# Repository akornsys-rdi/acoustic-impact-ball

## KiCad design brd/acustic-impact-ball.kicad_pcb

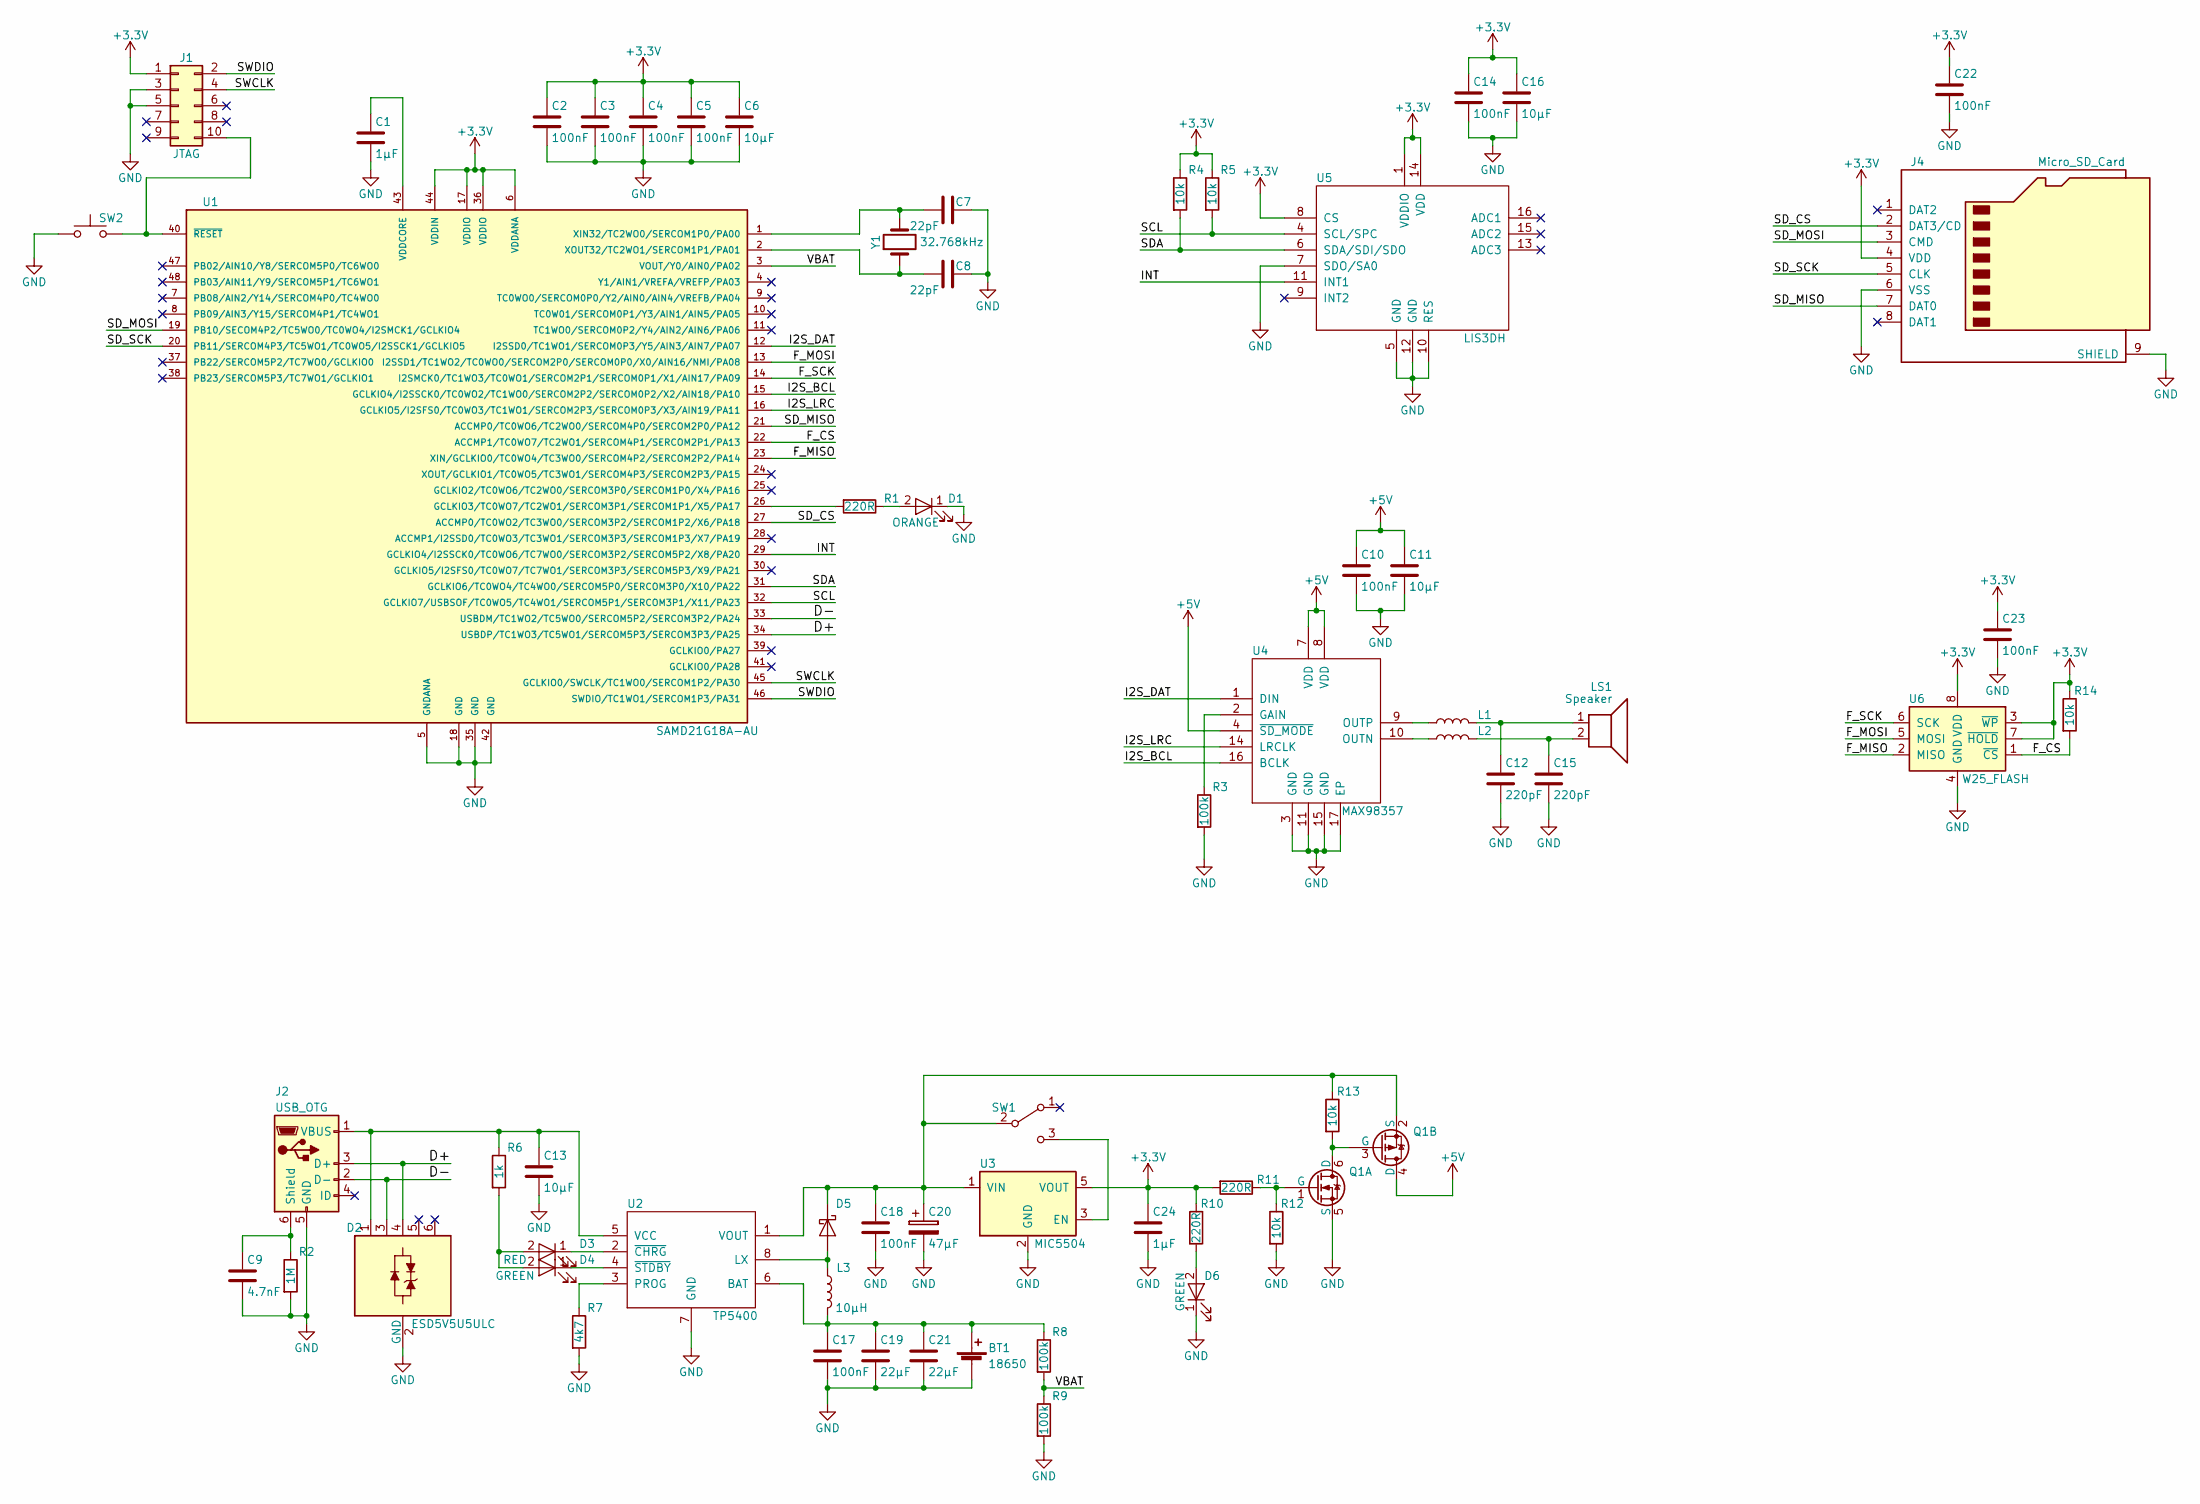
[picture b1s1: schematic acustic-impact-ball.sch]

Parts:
BT1: 18650; 18650-holder
C1, C24: 1µF; C_0805; Manufacturer Part Number C0805C105K8RACTU
C2, C3, C4, C5, C10, C14, C17, C18, C22, C23: 100nF; C_0805; Manufacturer Part Number C0805C104J5RACTU
C6, C11, C13, C16: 10µF; C_0805; Manufacturer Part Number C0805C106K8PACTU
C7, C8: 22pF; C_0805; Manufacturer Part Number C0805C220J5GACTU
C9: 4.7nF; C_0805; Manufacturer Part Number C0805C472K5RACTU
C12, C15: 220pF; C_0805; Manufacturer Part Number C0805C221J5GAC
C19, C21: 22µF; C_0805; Manufacturer Part Number C0805C226M9PACTU
C20: 47µF; CP_Tantalum_Case-B_EIA-3528-21_Reflow; Manufacturer Part Number TAJB476M010TNJ
D1: ORANGE; LED_0805; Manufacturer Part Number LO R976-PS-1
D2: ESD5V5U5ULC; SOT-23-6; Manufacturer Part Number ESD5V5U5ULC E6327
D3: RED; LED_0805; Manufacturer Part Number AP2012SRCPRV
D4, D6: GREEN; LED_0805; Manufacturer Part Number LG R971-KN-1
D5: D_Schottky; D_SOD-123F; Manufacturer Part Number SS34FA
J1: JTAG; Pin_Header_Straight_2x05_Pitch1.27mm_SMD; Manufacturer Part Number 20021121-00010D4LF
J2: USB_OTG; USB_Mini-B; Manufacturer Part Number UJ2-MBH-1-SMT-TR
J4: Micro_SD_Card; 5009010801; Manufacturer Part Number 500901-0801
L1, L2: Ferrite; L_0805_HandSoldering; Manufacturer Part Number BKP2125HS331-T
L3: 10µH; L_Taiyo-Yuden_NR-80xx; Manufacturer Part Number NR8040T100M
LS1: Speaker; Pin_Header_Angled_1x02_Pitch2.54mm; Manufacturer Part Number AS04004PR-R
Q1: DMG6602; SOT-23-6; Manufacturer Part Number DMG6602SVTQ-7
R1, R10, R11: 220R; R_0805_HandSoldering; Manufacturer Part Number CR0805-JW-221ELF
R2: 1M; R_0805_HandSoldering; Manufacturer Part Number CR0805-JW-105ELF
R3: 100k; R_0805_HandSoldering; Manufacturer Part Number CR0805-JW-104ELF
R4, R5, R12, R13, R14: 10k; R_0805_HandSoldering; Manufacturer Part Number CR0805-JW-103ELF
R6: 1k; R_0805_HandSoldering; Manufacturer Part Number CR0805-JW-102ELF
R7: 4k7; R_0805_HandSoldering; Manufacturer Part Number CR0805-JW-472ELF
R8, R9: 100k; R_0805_HandSoldering; Manufacturer Part Number CR0805-FX-1003ELF
SW1: SW_SPDT; SW_SPDT_PCM12; Manufacturer Part Number MSS3-V-T/R
SW2: SW_Push; PTS636_SP50
U1: SAMD21G18A-AU; TQFP-48_7x7mm_Pitch0.5mm; Manufacturer Part Number ATSAMD21G18A-AU
U2: TP5400; SOIC-8-1EP_3.9x4.9mm_Pitch1.27mm
U3: MIC5504; SOT-23-5; Manufacturer Part Number MIC5504-3.3YM5-TR
U4: MAX98357; QFN-16-1EP_3x3mm_Pitch0.5mm; Manufacturer Part Number MAX98357AETE+T
U5: LIS3DH; LGA-16_3x3mm_Pitch0.5mm_Handsoldering; Manufacturer Part Number LIS3DHTR
U6: W25_FLASH; SOIJ-8_5.3x5.3mm_Pitch1.27mm; Manufacturer Part Number W25Q128JVSIQ
Y1: 32.768kHz; Crystal_SMD_3215-2pin_3.2x1.5mm; Manufacturer Part Number FC-135 32.7680KA-A5

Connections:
+3V3: C2.1, C3.1, C4.1, C5.1, C6.1, C14.1, C16.1, C22.1, C23.1, C24.1, J1.1, J4.4 (VDD), R4.1, R5.1, R10.1, R11.2, R14.1, U1.6 (VDDANA), U1.17 (VDDIO), U1.36 (VDDIO), U1.44 (VDDIN), U3.5 (VOUT), U5.1 (VDDIO), U5.8 (CS), U5.14 (VDD), U6.3 (~WP), U6.7 (~HOLD), U6.8 (VDD)
+5V: C10.1, C11.1, Q1.4 (D), U4.4 (~SD_MODE), U4.7 (VDD), U4.8 (VDD)
/D+: D2.4, J2.3 (D+), U1.34 (USBDP/TC1WO3/TC5WO1/SERCOM5P3/SERCOM3P3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)
/D-: D2.3, J2.2 (D-), U1.33 (USBDM/TC1WO2/TC5WO0/SERCOM5P2/SERCOM3P2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)
/F_CS: R14.2, U1.22 (ACCMP1/TC0WO7/TC2WO1/SERCOM4P1/SERCOM2P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), U6.1 (~CS)
/F_MISO: U1.23 (XIN/GCLKIO0/TC0WO4/TC3WO0/SERCOM4P2/SER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), U6.2 (MISO)
/F_MOSI: U1.13 (I2SSD1/TC1WO2/TC0WO0/SERCOM2P0/SERCOM0P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), U6.5 (MOSI)
/F_SCK: U1.14 (I2SMCK0/TC1WO3/TC0WO1/SERCOM2P1/SERCOM0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), U6.6 (SCK)
/I2S_BCL: U1.15 (GCLKIO4/I2SSCK0/TC0WO2/TC1WO0/SERCOM2P2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), U4.16 (BCLK)
/I2S_DAT: U1.12 (I2SSD0/TC1WO1/SERCOM0P3/Y5/AIN3/AIN7/PA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), U4.1 (DIN)
/I2S_LRC: U1.16 (GCLKIO5/I2SFS0/TC0WO3/TC1WO1/SERCOM2P3/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), U4.14 (LRCLK)
/INT: U1.29 (GCLKIO4/I2SSCK0/TC0WO6/TC7WO0/SERCOM3P2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), U5.11 (INT1)
/SCL: R5.2, U1.32 (GCLKIO7/USBSOF/TC0WO5/TC4WO1/SERCOM5P1/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), U5.4 (SCL/SPC)
/SDA: R4.2, U1.31 (GCLKIO6/TC0WO4/TC4WO0/SERCOM5P0/SERCOM3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), U5.6 (SDA/SDI/SDO)
/SD_CS: J4.2 (DAT3/CD), U1.27 (ACCMP0/TC0WO2/TC3WO0/SERCOM3P2/SERCOM1P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)
/SD_MISO: J4.7 (DAT0), U1.21 (ACCMP0/TC0WO6/TC2WO0/SERCOM4P0/SERCOM2P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)
/SD_MOSI: J4.3 (CMD), U1.19 (PB10/SECOM4P2/TC5WO0/TC0WO4/I2SMCK1/GCL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)
/SD_SCK: J4.5 (CLK), U1.20 (PB11/SERCOM4P3/TC5WO1/TC0WO5/I2SSCK1/GC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)
/SWCLK: J1.4, U1.45 (GCLKIO0/SWCLK/TC1WO0/SERCOM1P2/PA30)
/SWDIO: J1.2, U1.46 (SWDIO/TC1WO1/SERCOM1P3/PA31)
/VBAT: R8.2, R9.1, U1.3 (VOUT/Y0/AIN0/PA02)
GND: BT1.2 (-), C1.2, C2.2, C3.2, C4.2, C5.2, C6.2, C7.2, C8.2, C9.2, C10.2, C11.2, C12.2, C13.2, C14.2, C15.2, C16.2, C17.2, C18.2, C19.2, C20.2, C21.2, C22.2, C23.2, C24.2, D1.1 (K), D2.2 (GND), D6.1 (K), J1.3, J1.5, J2.5 (GND), J4.6 (VSS), J4.9 (SHIELD), Q1.5 (S), R2.2, R3.2, R7.2, R9.2, R12.2, SW2.1, U1.5 (GNDANA), U1.18 (GND), U1.35 (GND), U1.42 (GND), U2.7 (GND), U3.2 (GND), U4.3 (GND), U4.11 (GND), U4.15 (GND), U4.17 (EP), U5.5 (GND), U5.7 (SDO/SA0), U5.10 (RES), U5.12 (GND), U6.4 (GND)
unnamed: BT1.1 (+), C17.1, C19.1, C21.1, L3.2, R8.1, U2.6 (BAT)
unnamed: C1.1, U1.43 (VDDCORE)
unnamed: C7.1, U1.1 (XIN32/TC2WO0/SERCOM1P0/PA00), Y1.2
unnamed: C8.1, U1.2 (XOUT32/TC2WO1/SERCOM1P1/PA01), Y1.1
unnamed: C9.1, J2.6 (Shield), R2.1
unnamed: C12.1, L1.2, LS1.1
unnamed: C13.1, D2.1, J2.1 (VBUS), R6.1, U2.5 (VCC)
unnamed: C15.1, L2.2, LS1.2
unnamed: C18.1, C20.1, D5.1 (K), Q1.2 (S), R13.1, SW1.2 (B), U2.1 (VOUT), U3.1 (VIN)
unnamed: D1.2 (A), R1.1
unnamed: D3.1 (K), U2.2 (~CHRG)
unnamed: D3.2 (A), D4.2 (A), R6.2
unnamed: D4.1 (K), U2.4 (~STDBY)
unnamed: D5.2 (A), L3.1, U2.8 (LX)
unnamed: D6.2 (A), R10.2
unnamed: J1.10, SW2.2, U1.40 (~RESET~)
unnamed: L1.1, U4.9 (OUTP)
unnamed: L2.1, U4.10 (OUTN)
unnamed: Q1.1 (G), R11.1, R12.1
unnamed: Q1.3 (G), Q1.6 (D), R13.2
unnamed: R1.2, U1.26 (GCLKIO3/TC0WO7/TC2WO1/SERCOM3P1/SERCOM1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)
unnamed: R3.1, U4.2 (GAIN)
unnamed: R7.1, U2.3 (PROG)
unnamed: SW1.3 (C), U3.3 (EN)

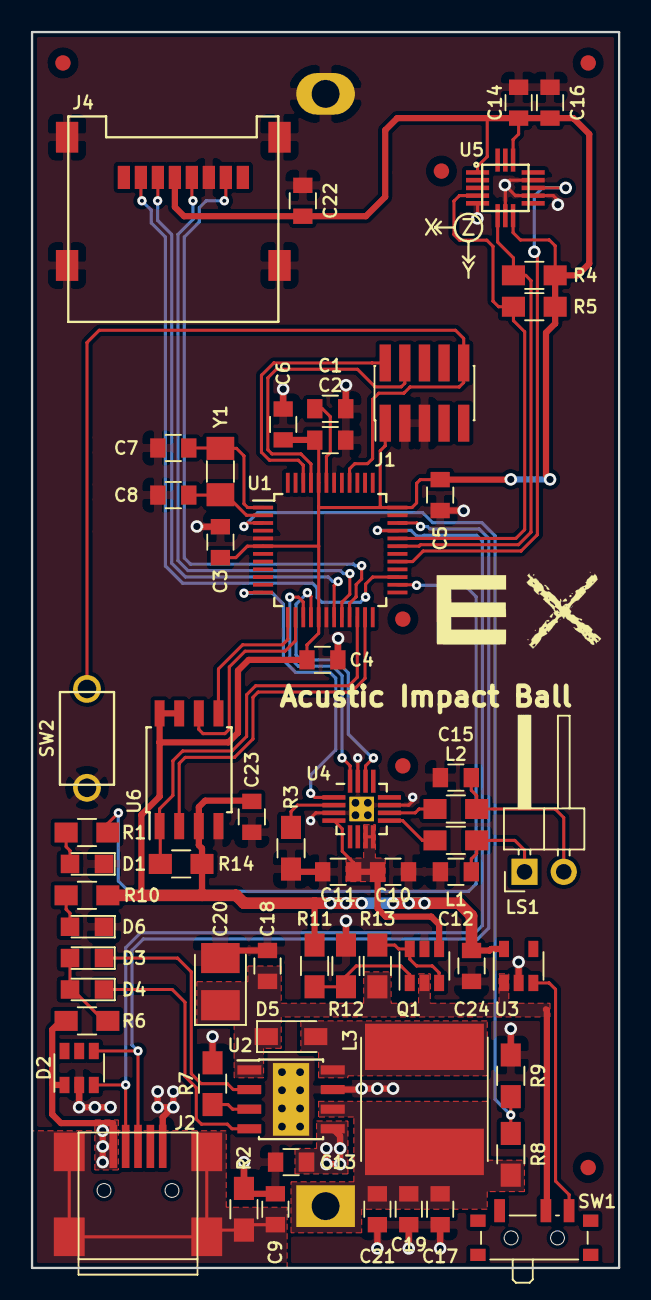
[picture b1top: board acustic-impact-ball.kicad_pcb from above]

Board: 2 copper layers, 38.0 x 80.0 mm, 62 parts (1 on the bottom side), 46 nets.

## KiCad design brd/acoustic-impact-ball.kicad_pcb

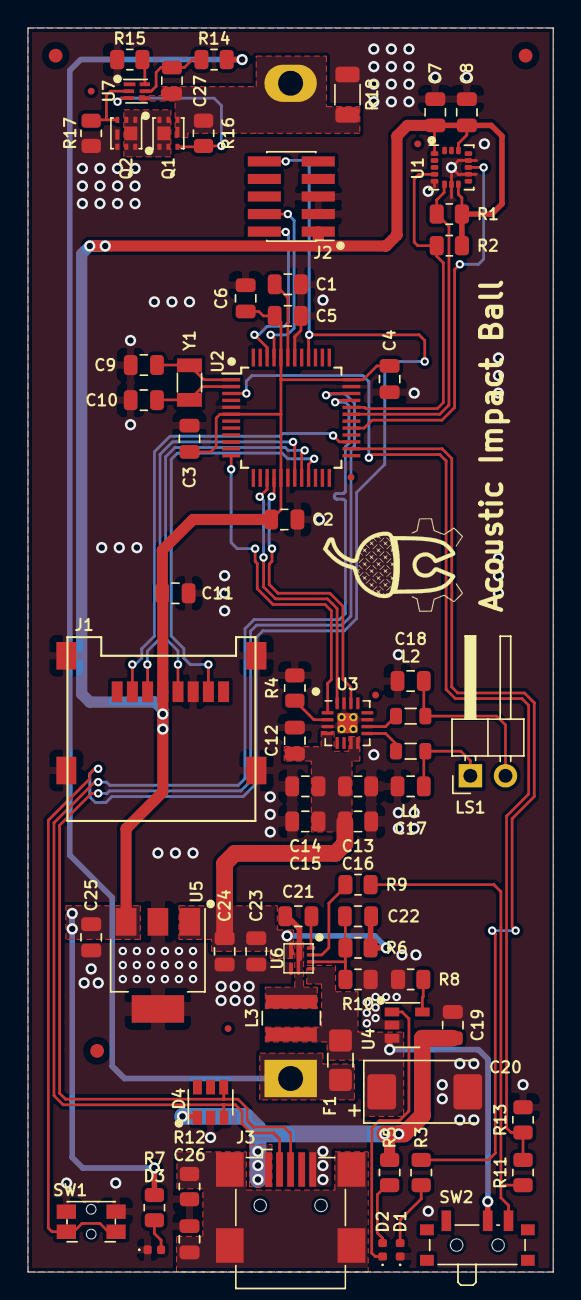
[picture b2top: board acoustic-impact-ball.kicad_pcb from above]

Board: 2 copper layers, 38.0 x 90.0 mm, 70 parts (1 on the bottom side), 48 nets.

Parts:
BT1: Li-Ion; 18650-holder
C1, C25: 1µF; C_0805_2012Metric
C2, C3, C4, C5, C7, C11, C12, C27: 100nF; C_0805_2012Metric
C6, C8, C19: 10µF; C_0805_2012Metric
C9, C10: 22pF; C_0805_2012Metric
C13, C14, C15, C16, C23, C24: 22µF; C_0805_2012Metric
C17, C18: 220pF; C_0805_2012Metric
C20: 150µF; CP_EIA-7343-31_Kemet-D
C21: 10nF; C_0805_2012Metric
C22: 10pF; C_0805_2012Metric
C26: 4.7nF; C_0805_2012Metric
D1: BLUE; LED_0402_1005Metric
D2: RED; LED_0402_1005Metric
D3: GREEN; LED_0402_1005Metric
D4: ESD5V5U5ULC; SOT-23-6
F1: 1.5A; Fuse_1206_3216Metric_Castellated
J1: Micro_SD_Card; 5009010801
J2: JTAG; PinHeader_2x05_P1.27mm_Vertical_SMD
J3: USB_B_Mini; USB_Mini-B_Wuerth_65100516121_Horizontal
L1, L2: Choke; L_0805_2012Metric
L3: 1µH; L_Wuerth_MAPI-4020
LS1: Speaker; PinHeader_1x02_P2.54mm_Horizontal
Q1, Q2: CSD16301Q2; Texas_DQK
R1, R2: 10k; R_0805_2012Metric
R3, R5, R7: 120R; R_0805_2012Metric
R4, R11, R13: 100k; R_0805_2012Metric
R6: 316k; R_0805_2012Metric
R8: 2k; R_0805_2012Metric
R9: 1k; R_0805_2012Metric
R10: 95k3; R_0805_2012Metric
R12: 1M; R_0805_2012Metric
R14: 330R; R_0805_2012Metric
R15: 2k2; R_0805_2012Metric
R16, R17: 5M1; R_0805_2012Metric
R18: 0R; R_1206_3216Metric
SW1: Reset; EVQP7
SW2: SW_SPDT; SW_SPDT_PCM12
U1: LIS3DH; LGA-16_3x3mm_P0.5mm_LayoutBorder3x5y
U2: ATSAMD21G18A-AU; TQFP-48_7x7mm_P0.5mm
U3: MAX98357; QFN-16-1EP_3x3mm_P0.5mm_EP1.45x1.45mm_ThermalVias
U4: MCP73831-2-OT; SOT-23-5
U5: MIC5201; SOT-223-3_TabPin2
U6: TPS61230A
U7: BQ297xy; WSON-6_1.5x1.5mm_P0.5mm
Y1: 32.768kHz; Crystal_SMD_3215-2Pin_3.2x1.5mm

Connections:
+3V3: C2.1, C3.1, C4.1, C5.1, C6.1, C7.1, C8.1, C11.1, C25.1, J1.4, J2.1, R1.1, R2.1, R7.1, U1.1, U1.8, U1.14, U2.6, U2.17, U2.36, U2.44, U5.3
+5V: C12.1, C13.1, C14.1, C15.1, C16.1, C22.1, C23.1, C24.1, R6.1, U3.4, U3.7, U3.8, U5.1, U6.7
/D+: D4.4, J3.3, U2.34
/D-: D4.3, J3.2, U2.33
/I2S_BCL: U2.15, U3.16
/I2S_DAT: U2.12, U3.1
/I2S_LRC: U2.16, U3.14
/IMU_INT: U1.11, U2.29
/IMU_SCL: R2.2, U1.4, U2.32
/IMU_SDA: R1.2, U1.6, U2.31
/RST: J2.10, SW1.1, U2.40
/SD_CS: J1.2, U2.27
/SD_MISO: J1.7, U2.21
/SD_MOSI: J1.3, U2.19
/SD_SCK: J1.5, U2.20
/SWCLK: J2.4, U2.45
/SWDIO: J2.2, U2.46
/ULED: R3.2, U2.26
/VBAT: R11.2, R13.1, U2.3
GND: C1.2, C2.2, C3.2, C4.2, C5.2, C6.2, C7.2, C8.2, C9.1, C10.1, C11.2, C12.2, C13.2, C14.2, C15.2, C16.2, C17.2, C18.2, C19.2, C20.2, C23.2, C24.2, C25.2, C26.2, D1.1, D3.1, D4.2, J1.6, J1.9, J2.3, J2.5, J3.5, Q2.4, Q2.7, R4.2, R8.2, R10.2, R12.2, R13.2, R15.2, R17.2, R18.2, SW1.2, U1.5, U1.7, U1.10, U1.12, U2.5, U2.18, U2.35, U2.42, U3.3, U3.11, U3.15, U3.17, U4.2, U5.2, U6.6
unnamed: BT1.1, F1.2, R14.1
unnamed: BT1.2, C27.2, Q1.4, Q1.7, R16.1, R18.1, U7.4
unnamed: C1.1, U2.43
unnamed: C9.2, U2.1, Y1.1
unnamed: C10.2, U2.2, Y1.2
unnamed: C17.1, L1.2, LS1.1
unnamed: C18.1, L2.2, LS1.2
unnamed: C19.1, D4.1, J3.1, R5.1, U4.4
unnamed: C20.1, F1.1, L3.1, SW2.2, U4.3, U6.4
unnamed: C21.1, U6.1
unnamed: C21.2, L3.2, U6.5
unnamed: C22.2, R6.2, R10.1, U6.3
unnamed: C26.1, J3.6, R12.1
unnamed: C27.1, R14.2, U7.5
unnamed: D1.2, R3.1
unnamed: D2.1, U4.1
unnamed: D2.2, R5.2
unnamed: D3.2, R7.2
unnamed: L1.1, U3.9
unnamed: L2.1, U3.10
unnamed: Q1.1, Q1.2, Q1.5, Q1.6, Q1.8, Q2.1, Q2.2, Q2.5, Q2.6, Q2.8
unnamed: Q1.3, R16.2, U7.3
unnamed: Q2.3, R17.1, U7.2
unnamed: R4.1, U3.2
unnamed: R8.1, U4.5
unnamed: R9.1, U6.2
unnamed: R9.2, R11.1, SW2.3
unnamed: R15.1, U7.6

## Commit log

2020-02-25 añadida pcb
2020-02-25 subido código de prototipo
2020-02-25 subido modelo 3d de prototipo
2020-08-20 subido nuevo diseño 3d
2023-03-11 subidos datasheets
2023-03-11 subido código de pruebas y producción
2023-03-11 actualizado 3d
2023-03-11 creado archivo de notas sobre el proyecto
2023-03-11 actualizada tapa 3D
2023-03-18 añadidos comentarios de versiones usadas y actualizados comentarios de funciones
2023-10-07 actualizada carcasa para nueva pcb, corregidos puntos debiles de version anterior, generados archivos numerados
2023-10-07 rediseñada pcb y generados archivos de fabricacion
2023-10-07 generadas pegatinas
2023-10-07 eliminado archivo de notas de la anterior version
2023-10-07 actualizados parametros en codigo

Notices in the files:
brd/acoustic-impact-ball.kicad_pcb:
Released under GNU/GPL 3 License
https://www.gnu.org/licenses/gpl.html
Copyright © 2023 RileyStarlight
brd/acustic-impact-ball.kicad_pcb:
Copyright © 2020 kwendenarmo
